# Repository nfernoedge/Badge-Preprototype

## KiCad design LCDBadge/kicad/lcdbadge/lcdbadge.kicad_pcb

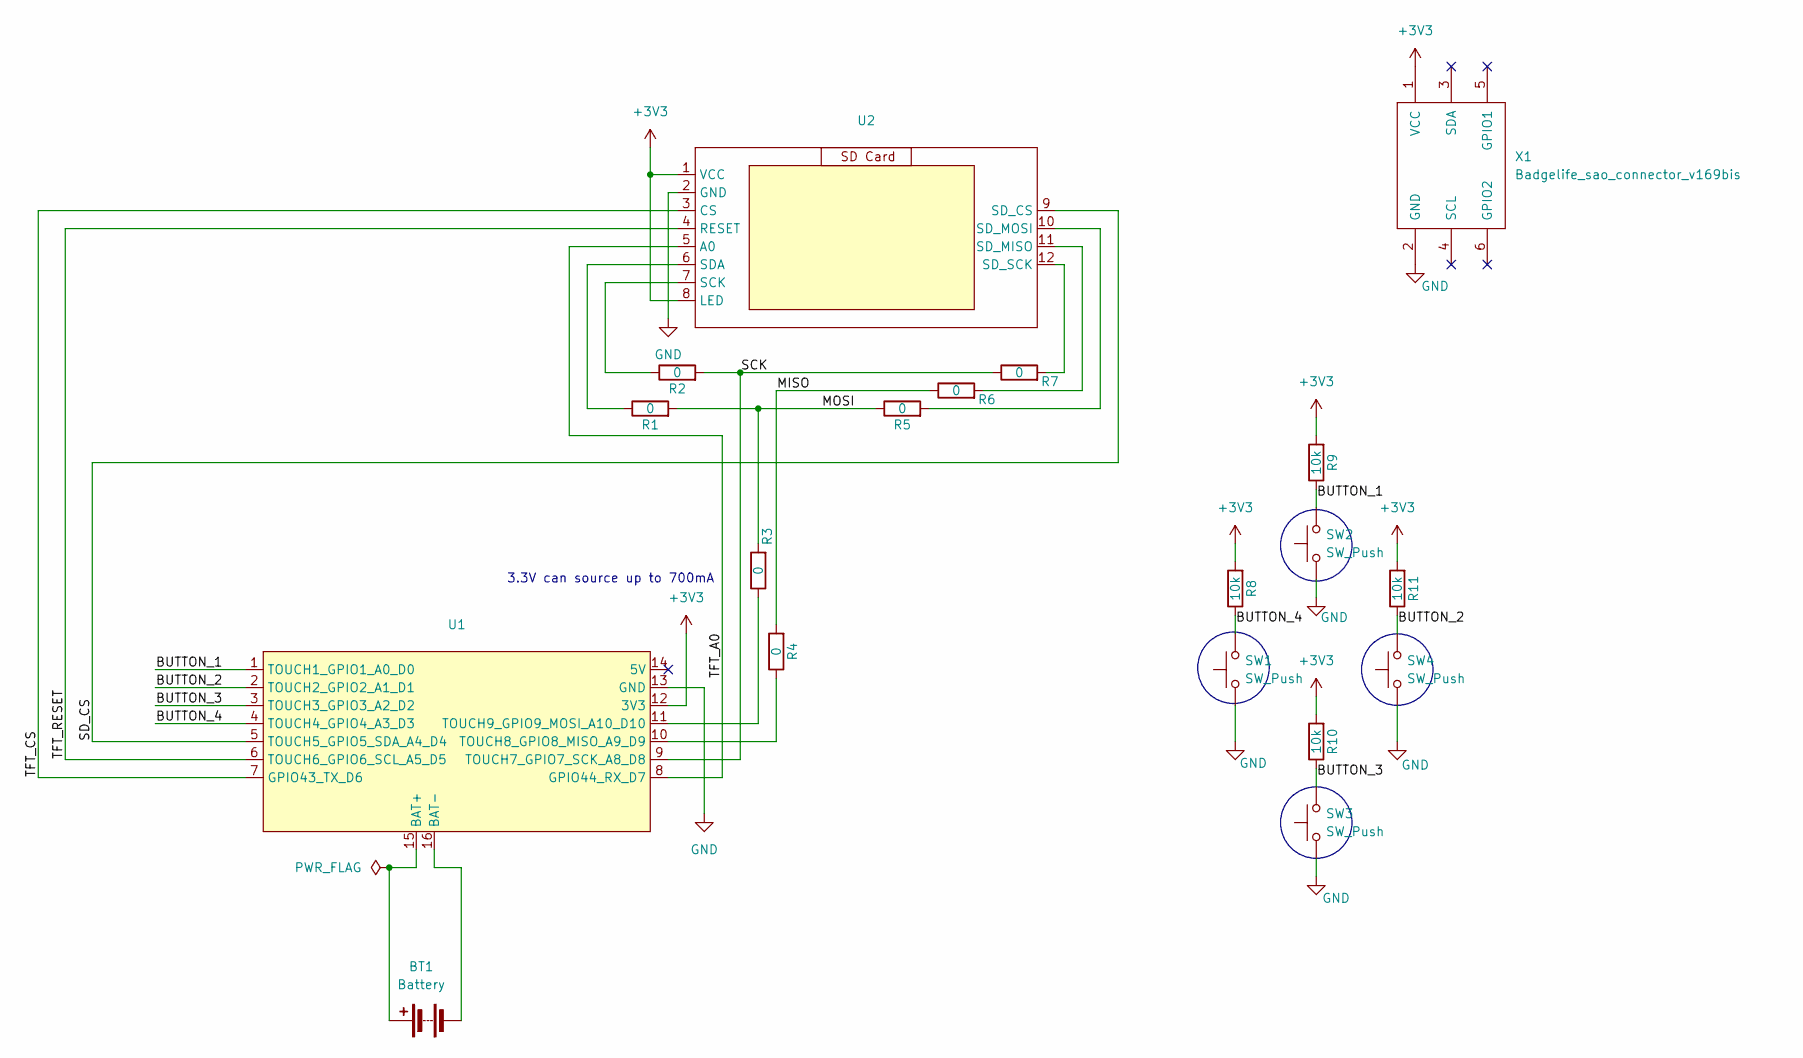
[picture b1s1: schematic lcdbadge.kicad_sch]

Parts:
BT1: Battery; 12BHC186P1-GR
R1, R2, R3, R4, R5, R6, R7: 0; R_0805_2012Metric_Pad1.20x1.40mm_HandSolder
R8, R9, R10, R11: 10k; R_0805_2012Metric_Pad1.20x1.40mm_HandSolder
SW1, SW2, SW3, SW4: SW_Push; SW_Tactile_Straight_KSA0Axx1LFTR
U1: MOUDLE14P-SMD-2.54-21X17.8MM_BAT
U2: AliExpress_1.8_128x160_ST7735
X1: Badgelife_sao_connector_v169bis; Badgelife-SAOv169-BADGE-2x3

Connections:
+3V3: R8.2, R9.2, R10.2, R11.2, U1.12 (3V3), U2.1 (VCC), U2.8 (LED), X1.1 (VCC)
/BUTTON_1: R9.1, SW2.2, U1.1 (TOUCH1_GPIO1_A0_D0)
/BUTTON_2: R11.1, SW4.2, U1.2 (TOUCH2_GPIO2_A1_D1)
/BUTTON_3: R10.1, SW3.2, U1.3 (TOUCH3_GPIO3_A2_D2)
/BUTTON_4: R8.1, SW1.2, U1.4 (TOUCH4_GPIO4_A3_D3)
/MISO: R4.2, R6.1
/MOSI: R1.2, R3.2, R5.1
/SCK: R2.2, R7.1, U1.9 (TOUCH7_GPIO7_SCK_A8_D8)
/SD_CS: U1.5 (TOUCH5_GPIO5_SDA_A4_D4), U2.9 (SD_CS)
/TFT_A0: U1.8 (GPIO44_RX_D7), U2.5 (A0)
/TFT_CS: U1.7 (GPIO43_TX_D6), U2.3 (CS)
/TFT_RESET: U1.6 (TOUCH6_GPIO6_SCL_A5_D5), U2.4 (RESET)
GND: SW1.1, SW2.1, SW3.1, SW4.1, U1.13 (GND), U2.2 (GND), X1.2 (GND)
unnamed: BT1.1 (+), U1.15 (BAT+)
unnamed: BT1.2 (-), U1.16 (BAT-)
unnamed: R4.1, U1.10 (TOUCH8_GPIO8_MISO_A9_D9)
unnamed: R3.1, U1.11 (TOUCH9_GPIO9_MOSI_A10_D10)
unnamed: R2.1, U2.7 (SCK)
unnamed: R1.1, U2.6 (SDA)
unnamed: R6.2, U2.11 (SD_MISO)
unnamed: R5.2, U2.10 (SD_MOSI)
unnamed: R7.2, U2.12 (SD_SCK)

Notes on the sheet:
3.3V can source up to 700mA

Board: 2 copper layers, 19 parts (1 on the bottom side), 22 nets, no tracks yet.

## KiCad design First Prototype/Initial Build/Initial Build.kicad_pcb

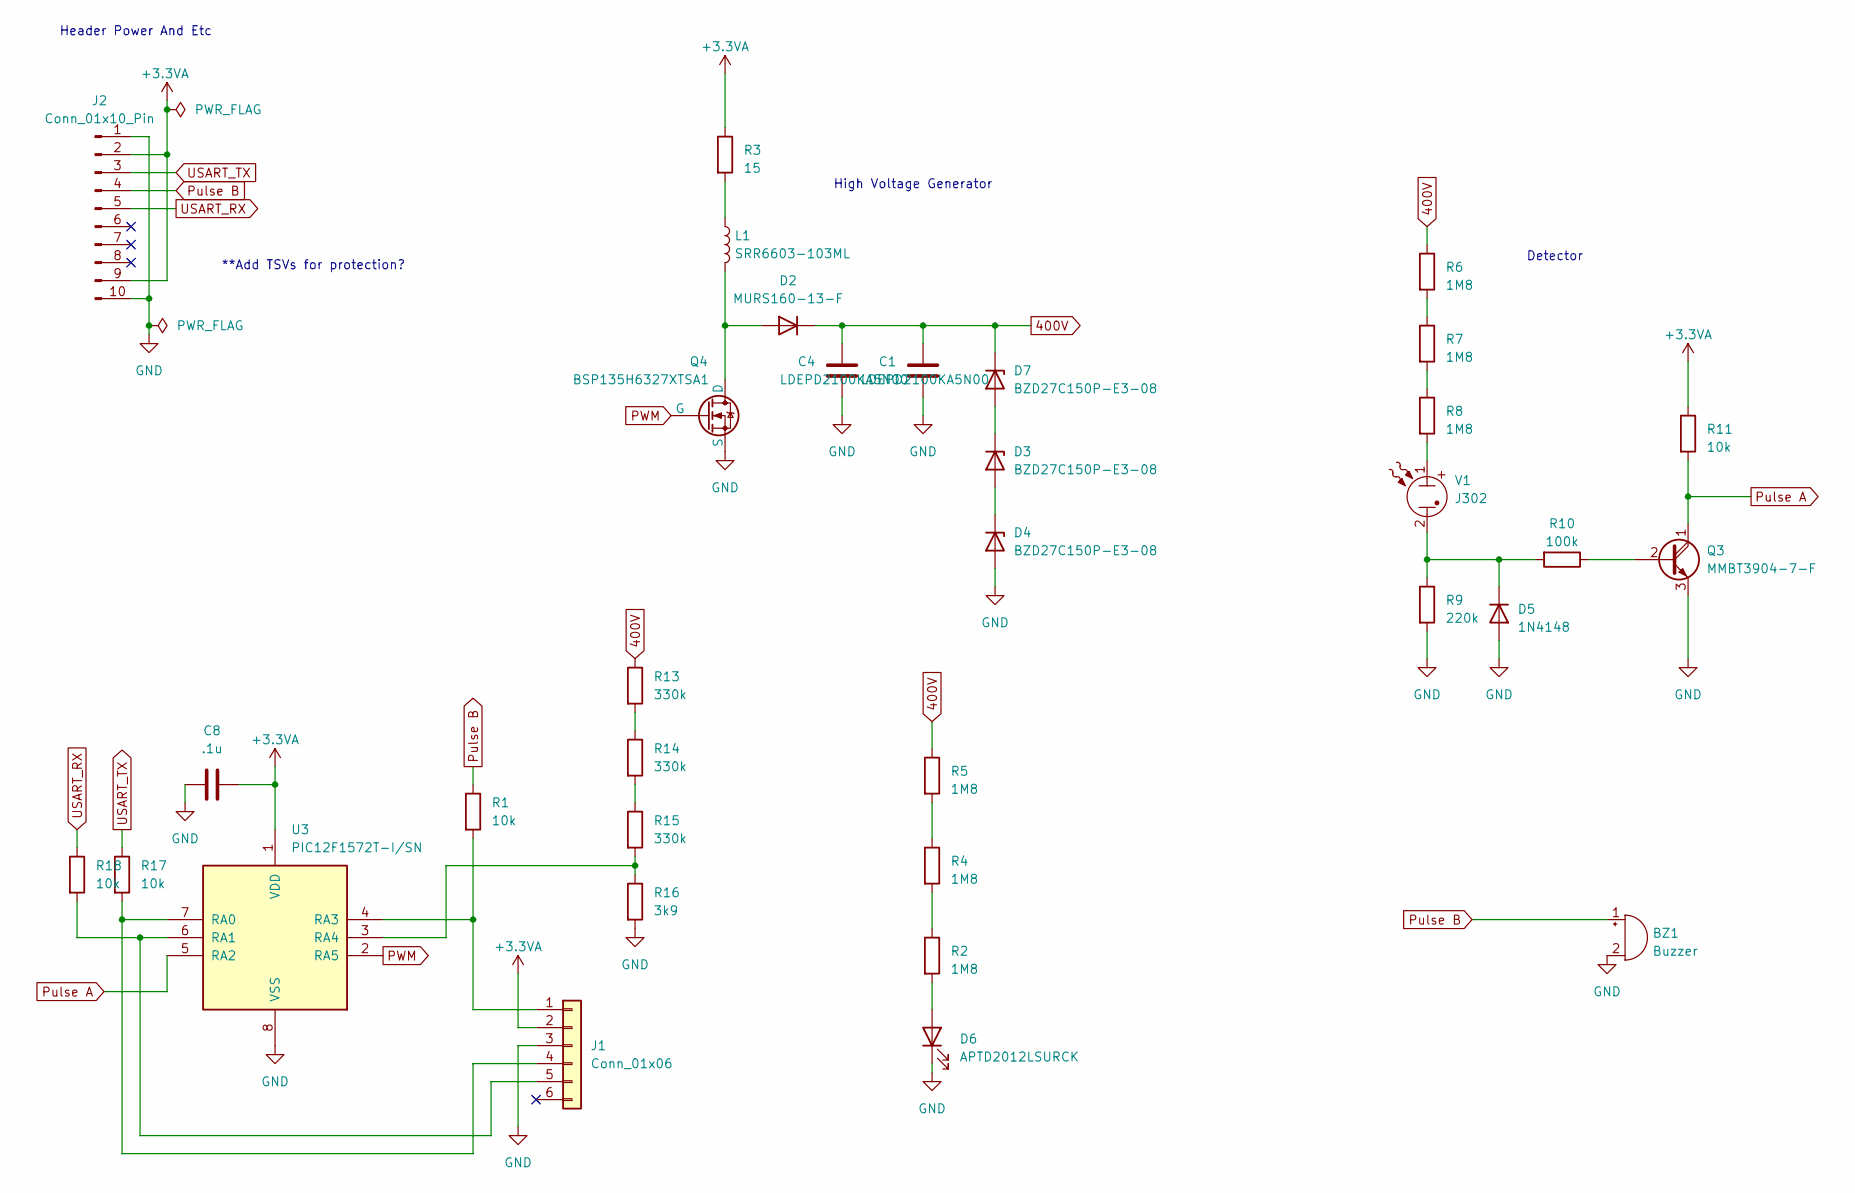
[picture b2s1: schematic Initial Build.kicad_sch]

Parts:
BZ1: Buzzer; Buzzer_12x9.5RM7.6
C1, C4: LDEPD2100KA5N00; C_2220_5650Metric_Pad1.97x5.40mm_HandSolder
C8: .1u; C_0805_2012Metric_Pad1.18x1.45mm_HandSolder
D2: MURS160-13-F; D_SMB_Handsoldering
D3, D4, D7: BZD27C150P-E3-08; D_SMF
D5: 1N4148; D_SMB-SMC_Universal_Handsoldering
D6: APTD2012LSURCK; LED_0805_2012Metric_Pad1.15x1.40mm_HandSolder
J1: Conn_01x06; PinHeader_1x06_P2.54mm_Vertical
J2: Conn_01x10_Pin; PinHeader_2x05_P2.54mm_Vertical
L1: SRR6603-103ML; L_Bourns_SRP7028A_7.3x6.6mm
Q3: MMBT3904-7-F; SOT-23-3
Q4: BSP135H6327XTSA1; SOT-223
R1, R11, R17, R18: 10k; R_1206_3216Metric_Pad1.30x1.75mm_HandSolder
R2, R4, R5, R6, R7, R8: 1M8; R_1206_3216Metric_Pad1.30x1.75mm_HandSolder
R3: 15; R_1206_3216Metric_Pad1.30x1.75mm_HandSolder
R9: 220k; R_1206_3216Metric_Pad1.30x1.75mm_HandSolder
R10: 100k; R_1206_3216Metric_Pad1.30x1.75mm_HandSolder
R13, R14, R15: 330k; R_1206_3216Metric_Pad1.30x1.75mm_HandSolder
R16: 3k9; R_1206_3216Metric_Pad1.30x1.75mm_HandSolder
U3: PIC12F1572T-I/SN; SOIC-8_3.9x4.9mm_P1.27mm
V1: J302; Geiger_Clips

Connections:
400V: C1.2, C4.2, D2.1 (K), D7.1 (K), R5.1, R6.1, R13.1
+3.3VA: C8.1, J1.2, J2.2, J2.9, R3.1, R11.1, U3.1 (VDD)
GND: BZ1.2 (+), C1.1, C4.1, C8.2, D4.2 (A), D5.2 (A), D6.1 (K), J1.3, J2.1, J2.10, Q3.3 (E), Q4.3 (S), R9.2, R16.2, U3.8 (VSS)
unnamed: D2.2 (A), L1.2, Q4.1 (D)
unnamed: D3.2 (A), D4.1 (K)
unnamed: D3.1 (K), D7.2 (A)
unnamed: D5.1 (K), R9.1, R10.2, V1.2
unnamed: D6.2 (A), R2.2
unnamed: J1.1, R1.2, U3.4 (RA3)
unnamed: J1.4, R17.2, U3.7 (RA0)
unnamed: J1.5, R18.2, U3.6 (RA1)
unnamed: L1.1, R3.2
unnamed: Q3.2 (B), R10.1
unnamed: R2.1, R4.2
unnamed: R4.1, R5.2
unnamed: R6.2, R7.1
unnamed: R7.2, R8.1
unnamed: R8.2, V1.1
unnamed: R13.2, R14.1
unnamed: R14.2, R15.1
unnamed: R15.2, R16.1, U3.3 (RA4)
PWM: Q4.2 (G), U3.2 (RA5)
Pulse A: Q3.1 (C), R11.2, U3.5 (RA2)
Pulse B: BZ1.1 (-), J2.4, R1.1
USART_RX: J2.5, R18.1
USART_TX: J2.3, R17.1

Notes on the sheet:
High Voltage Generator
**Add TSVs for protection?
Detector
Header Power And Etc

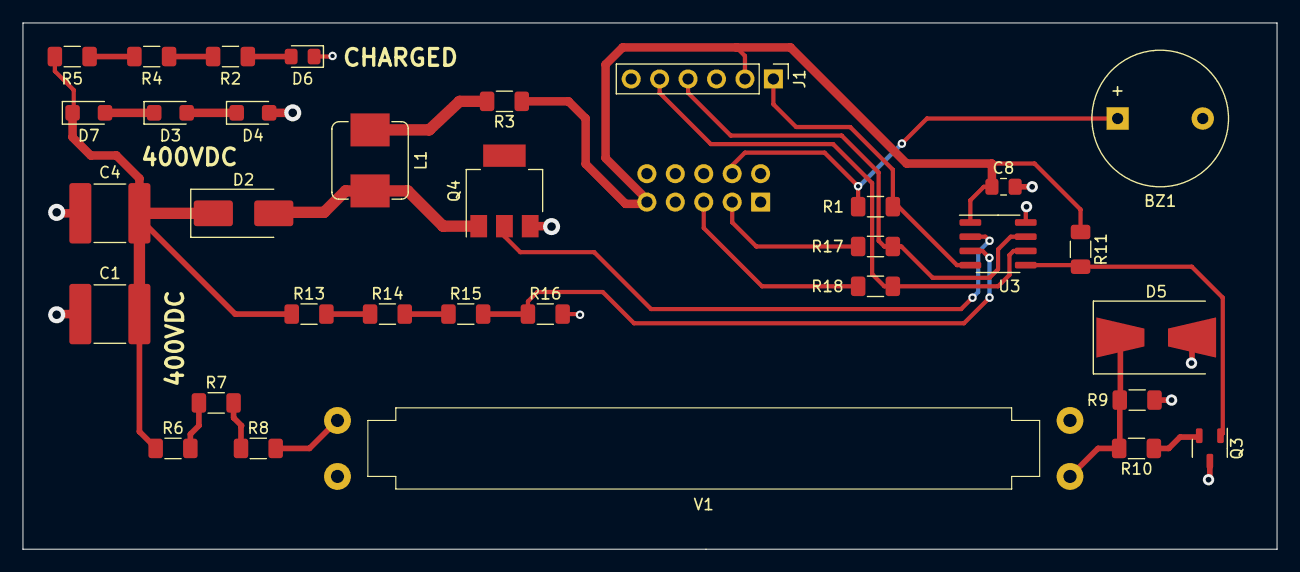
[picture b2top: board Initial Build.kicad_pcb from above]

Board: 2 copper layers, 112.0 x 47.0 mm, 34 parts (1 on the bottom side), 26 nets.

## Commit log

2023-09-01 Add files via upload
    Fixing excel formula
2023-09-18 added pic
2023-09-22 removed non-pic related components added indicator for 400v
2023-09-25 updated tube fp began routing
2023-09-25 finished routing
2023-12-09 initial firmware
2024-07-04 pushing schematic and initial pcb
2024-07-05 routed board updated button changed from route to large vias for module
2024-07-05 rotated esp moved resistors away from sd card holder
2024-07-25 Resized and Updated GIFs to be 16-bit color
2024-07-25 Initial commit of badge firmware
2024-07-25 Image converter to go from 24 bit color to 16 bit color
2024-07-26 Added RC4 Encryption to deter reverse engineering
2024-08-05 Added custom SDcard Status to allow early Error Detection.
2024-08-05 Added background color change to allow for BSOD
2024-08-05 added both SD error detection, and BSOD capabilities.
2024-08-08 Working Prize validation and level storing on EEPROM.
2024-08-08 GIFs for challenges
2024-08-08 Moved challenge gifs for the correct folder.
2024-08-08 Updated the values for each level
2024-08-19 Updated to be the correct screen and added first boot check for flash.
2024-08-19 Updated Color of gifs
2024-08-19 Updated Puzzle for 8 levels instead of 10
2024-08-29 Update Puzzle.h
    Fixing my fatfinger of the puzzle4 solution
2024-08-30 Update README.md
    crayon-level instructions per Whiskey's request
2024-09-10 Made some simple obfuscation tricks
